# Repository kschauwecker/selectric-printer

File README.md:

# IBM Selectric Network Printer
This is an ongoing project to convert an IBM Selectric III electromechanical typewriter into a working network printer. It will consist of a set of solenoids that are linked through 3D-printed parts with the the typewrites mechanisms. A custom circuit board controls the solenoids, which features an RP2040 micro controller and a Raspberry Pi Compute Module.

Have a look at my other typewriter projects to get an idea what this will be like:
https://elektronaut.tech/en/tinker-corner/

More information will follow...

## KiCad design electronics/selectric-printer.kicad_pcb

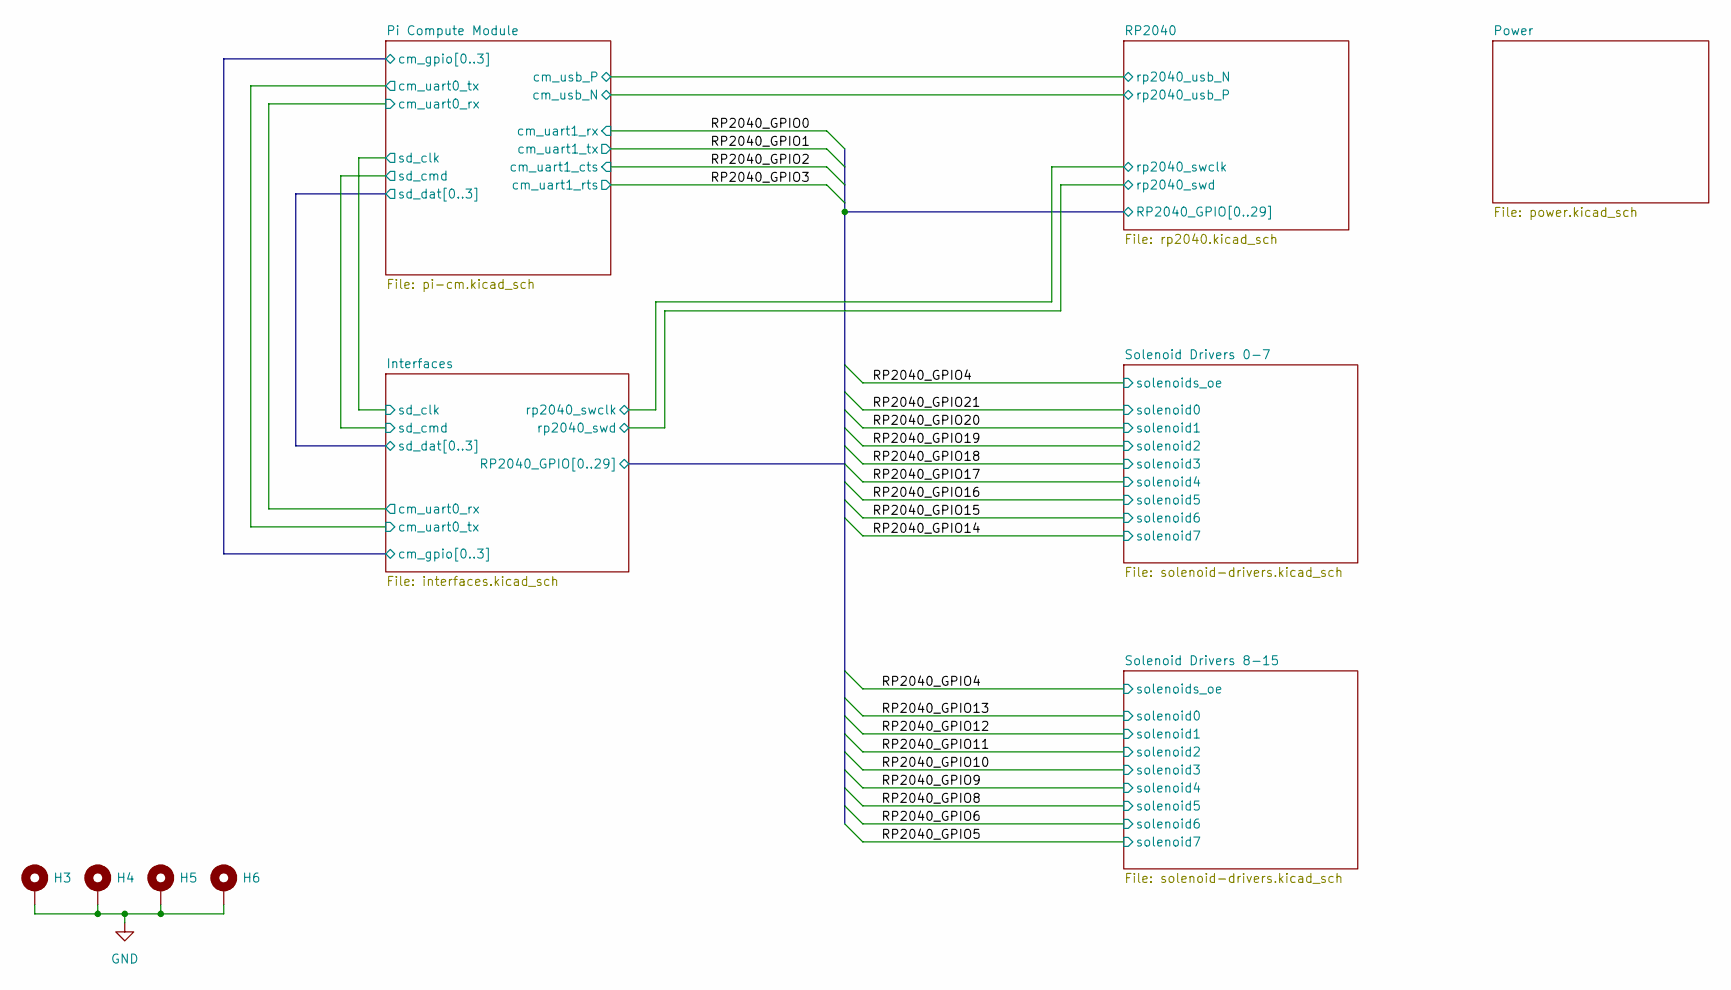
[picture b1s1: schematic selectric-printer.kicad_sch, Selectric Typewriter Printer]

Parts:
H3, H4, H5, H6: MountingHole_Pad; MountingHole_3.2mm_M3_Pad

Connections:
GND: H3.1, H4.1, H5.1, H6.1; also elsewhere on the board

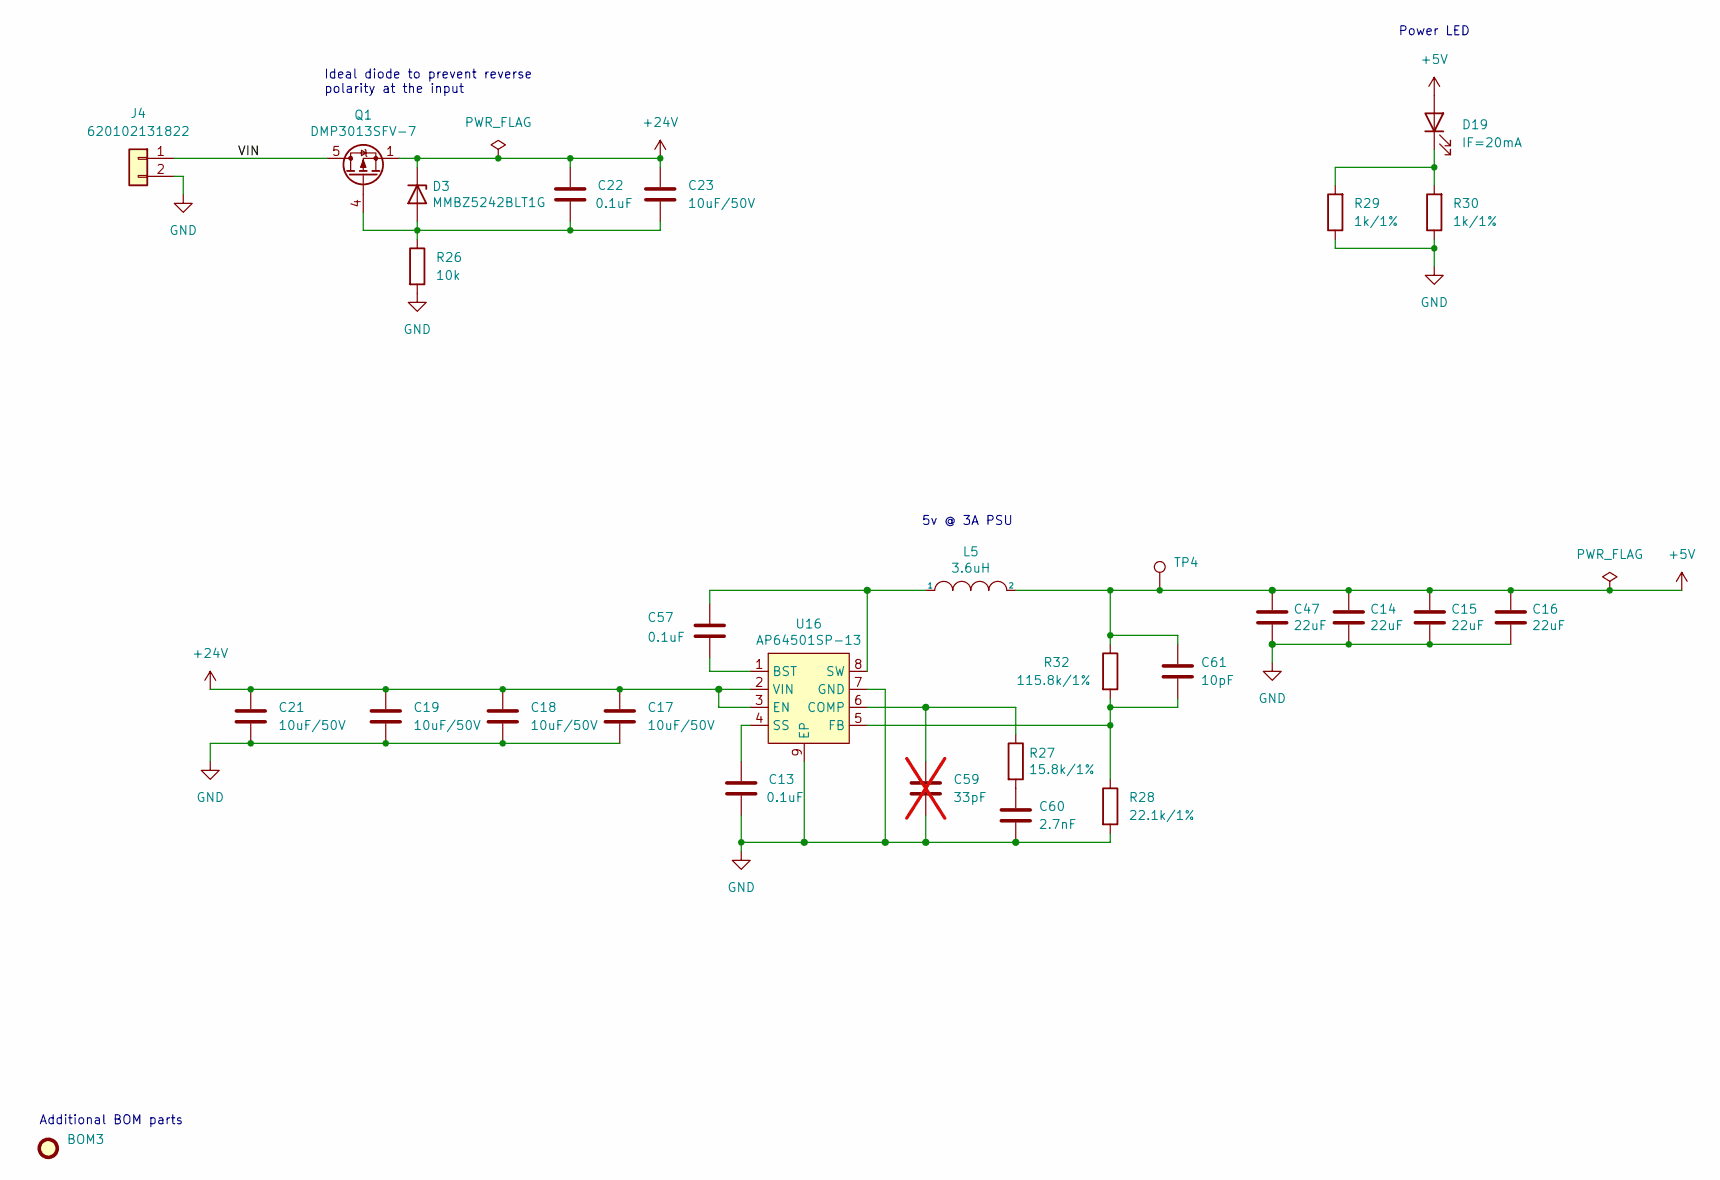
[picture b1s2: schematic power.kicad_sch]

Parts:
BOM3: MPN 620002113322
C13, C22, C57: 0.1uF; C_0402_1005Metric; MPN MBAST105SB7104KFNA01
C14, C15, C16, C47: 22uF; C_0805_2012Metric; MPN LMK212BC6226MG-T
C17, C18, C19, C21, C23: 10uF/50V; C_1206_3216Metric; MPN MLASG31LAB7106KTNB25
C59: 33pF; C_0402_1005Metric; not fitted
C60: 2.7nF; C_0402_1005Metric; MPN GRM1555C1H272GE01J
C61: 10pF; C_0402_1005Metric; MPN C0402C100K5HACAUTO
D3: MMBZ5242BLT1G; D_SOD-323; MPN MMSZ5242BS-7-F
D19: IF=20mA; LED_0603_1608Metric; MPN 150060GS83000
J4: 620102131822; WE-620102131822; MPN 620102131822
L5: 3.6uH; L_Taiyo-Yuden_NR-80xx; MPN NRS8040T3R6NJGJ
Q1: DMP3013SFV-7; Diodes_PowerDI3333-8; MPN DMP3013SFV-7
R26: 10k; R_0402_1005Metric; MPN CRCW040210K0FKEDC
R27: 15.8k/1%; R_0402_1005Metric; MPN ERA-2AEB1582X
R28: 22.1k/1%; R_0402_1005Metric; MPN 560112110099
R29, R30: 1k/1%; R_0402_1005Metric; MPN RC0402JR-7D1KL
R32: 115.8k/1%; R_0402_1005Metric; MPN RP73PF1E115RBTD
TP4: TestPoint; TestPoint_Pad_D2.0mm
U16: AP64501SP-13; SOIC-8-1EP_3.9x4.9mm_P1.27mm_EP2.29x3mm; MPN AP64501SP-13

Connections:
+5V: C14.1, C15.1, C16.1, C47.1, C61.1, D19.2 (A), L5.2, R32.1, TP4.1; also elsewhere on the board
+24V: C17.1, C18.1, C19.1, C21.1, C22.1, C23.1, D3.1 (K), Q1.1 (S), Q1.2 (S), Q1.3 (S), U16.2 (VIN), U16.3 (EN); also elsewhere on the board
/Power/VIN: J4.1, Q1.5 (D)
GND: C13.2, C14.2, C15.2, C16.2, C17.2, C18.2, C19.2, C21.2, C47.2, C59.2, C60.2, J4.2, R26.2, R28.2, R29.1, R30.1, U16.7 (GND), U16.9 (EP); also elsewhere on the board
unnamed: C60.1, R27.2
unnamed: C22.2, C23.2, D3.2 (A), Q1.4 (G), R26.1
unnamed: D19.1 (K), R29.2, R30.2
unnamed: C57.2, U16.1 (BST)
unnamed: C59.1, R27.1, U16.6 (COMP)
unnamed: C61.2, R28.1, R32.2, U16.5 (FB)
unnamed: C13.1, U16.4 (SS)
unnamed: C57.1, L5.1, U16.8 (SW)

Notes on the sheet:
5v @ 3A PSU
Power LED
Ideal diode to prevent reverse polarity at the input
Additional BOM parts

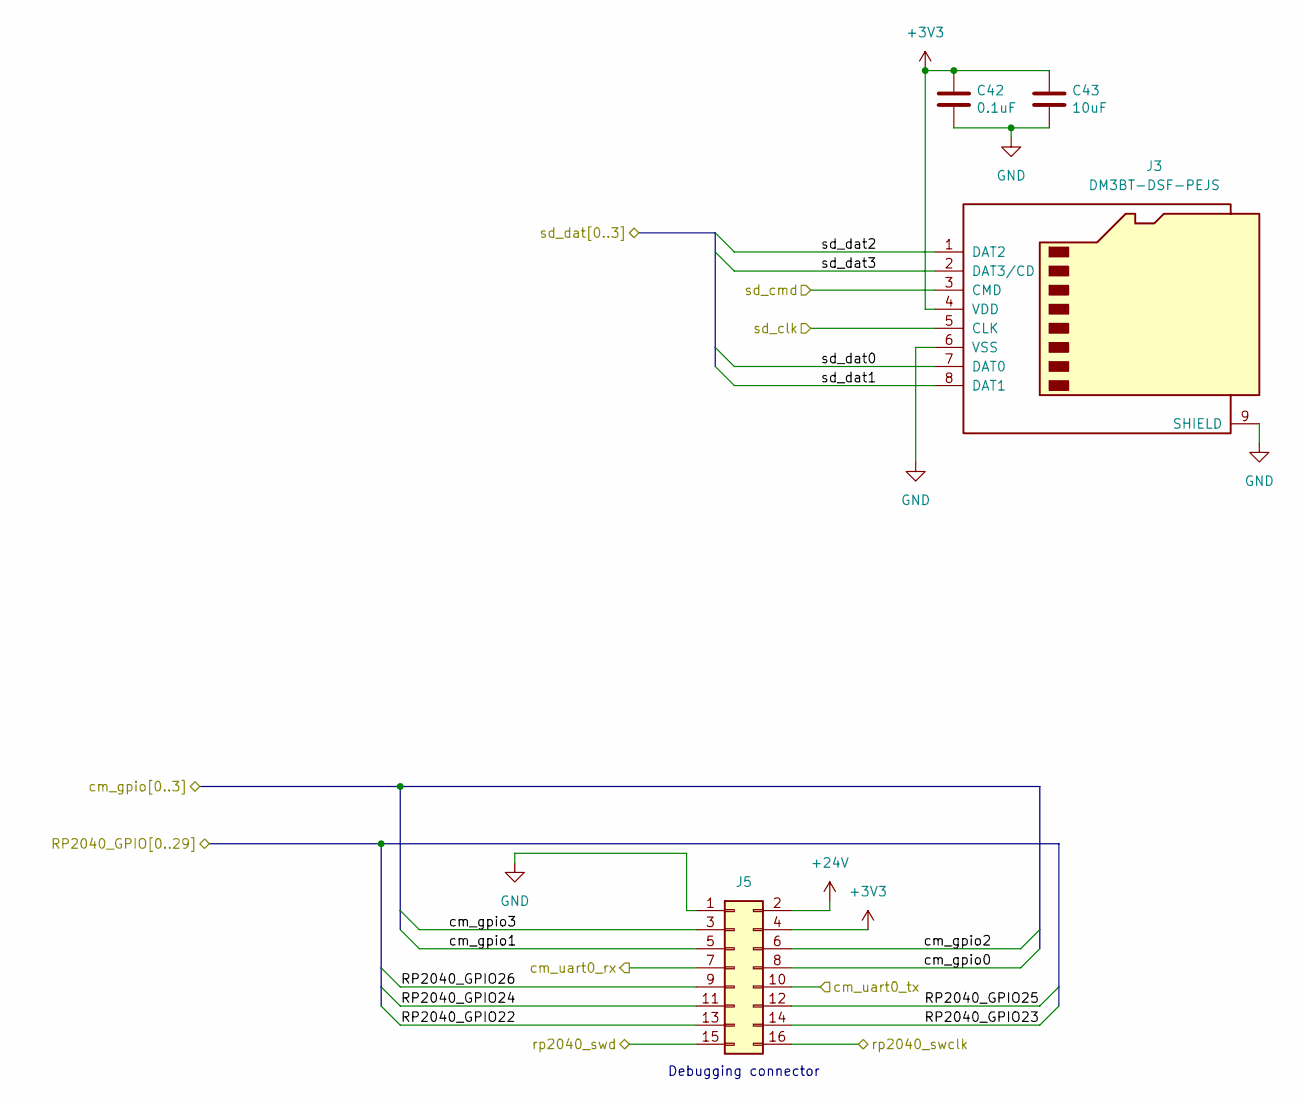
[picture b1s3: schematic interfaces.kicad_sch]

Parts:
C42: 0.1uF; C_0402_1005Metric; MPN MBAST105SB7104KFNA01
C43: 10uF; C_0603_1608Metric; MPN MSAST168BB5106MTNA01
J3: DM3BT-DSF-PEJS; microSD_HC_Hirose_DM3BT-DSF-PEJS; MPN DM3BT-DSF-PEJS
J5: Conn_02x08_Odd_Even; Samtec-TSM-108-01-F-DH; MPN TSM-108-01-F-DH

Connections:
+3V3: C42.1, C43.1, J3.4 (VDD), J5.4; also elsewhere on the board
+24V: J5.2; also elsewhere on the board
/Interfaces/RP2040_GPIO22: J5.13; also elsewhere on the board
/Interfaces/RP2040_GPIO23: J5.14; also elsewhere on the board
/Interfaces/RP2040_GPIO24: J5.11; also elsewhere on the board
/Interfaces/RP2040_GPIO25: J5.12; also elsewhere on the board
/Interfaces/RP2040_GPIO26: J5.9; also elsewhere on the board
/Interfaces/cm_gpio0: J5.8; also elsewhere on the board
/Interfaces/cm_gpio1: J5.5; also elsewhere on the board
/Interfaces/cm_gpio2: J5.6; also elsewhere on the board
/Interfaces/cm_gpio3: J5.3; also elsewhere on the board
/Interfaces/cm_uart0_rx: J5.7; also elsewhere on the board
/Interfaces/cm_uart0_tx: J5.10; also elsewhere on the board
/Interfaces/rp2040_swclk: J5.16; also elsewhere on the board
/Interfaces/rp2040_swd: J5.15; also elsewhere on the board
/Interfaces/sd_cmd: J3.3 (CMD); also elsewhere on the board
/Interfaces/sd_dat0: J3.7 (DAT0); also elsewhere on the board
/Interfaces/sd_dat1: J3.8 (DAT1); also elsewhere on the board
/Interfaces/sd_dat2: J3.1 (DAT2); also elsewhere on the board
/Interfaces/sd_dat3: J3.2 (DAT3/CD); also elsewhere on the board
/Pi Compute Module/sd_clk: J3.5 (CLK); also elsewhere on the board
GND: C42.2, C43.2, J3.6 (VSS), J3.9 (SHIELD), J5.1; also elsewhere on the board

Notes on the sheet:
Debugging connector

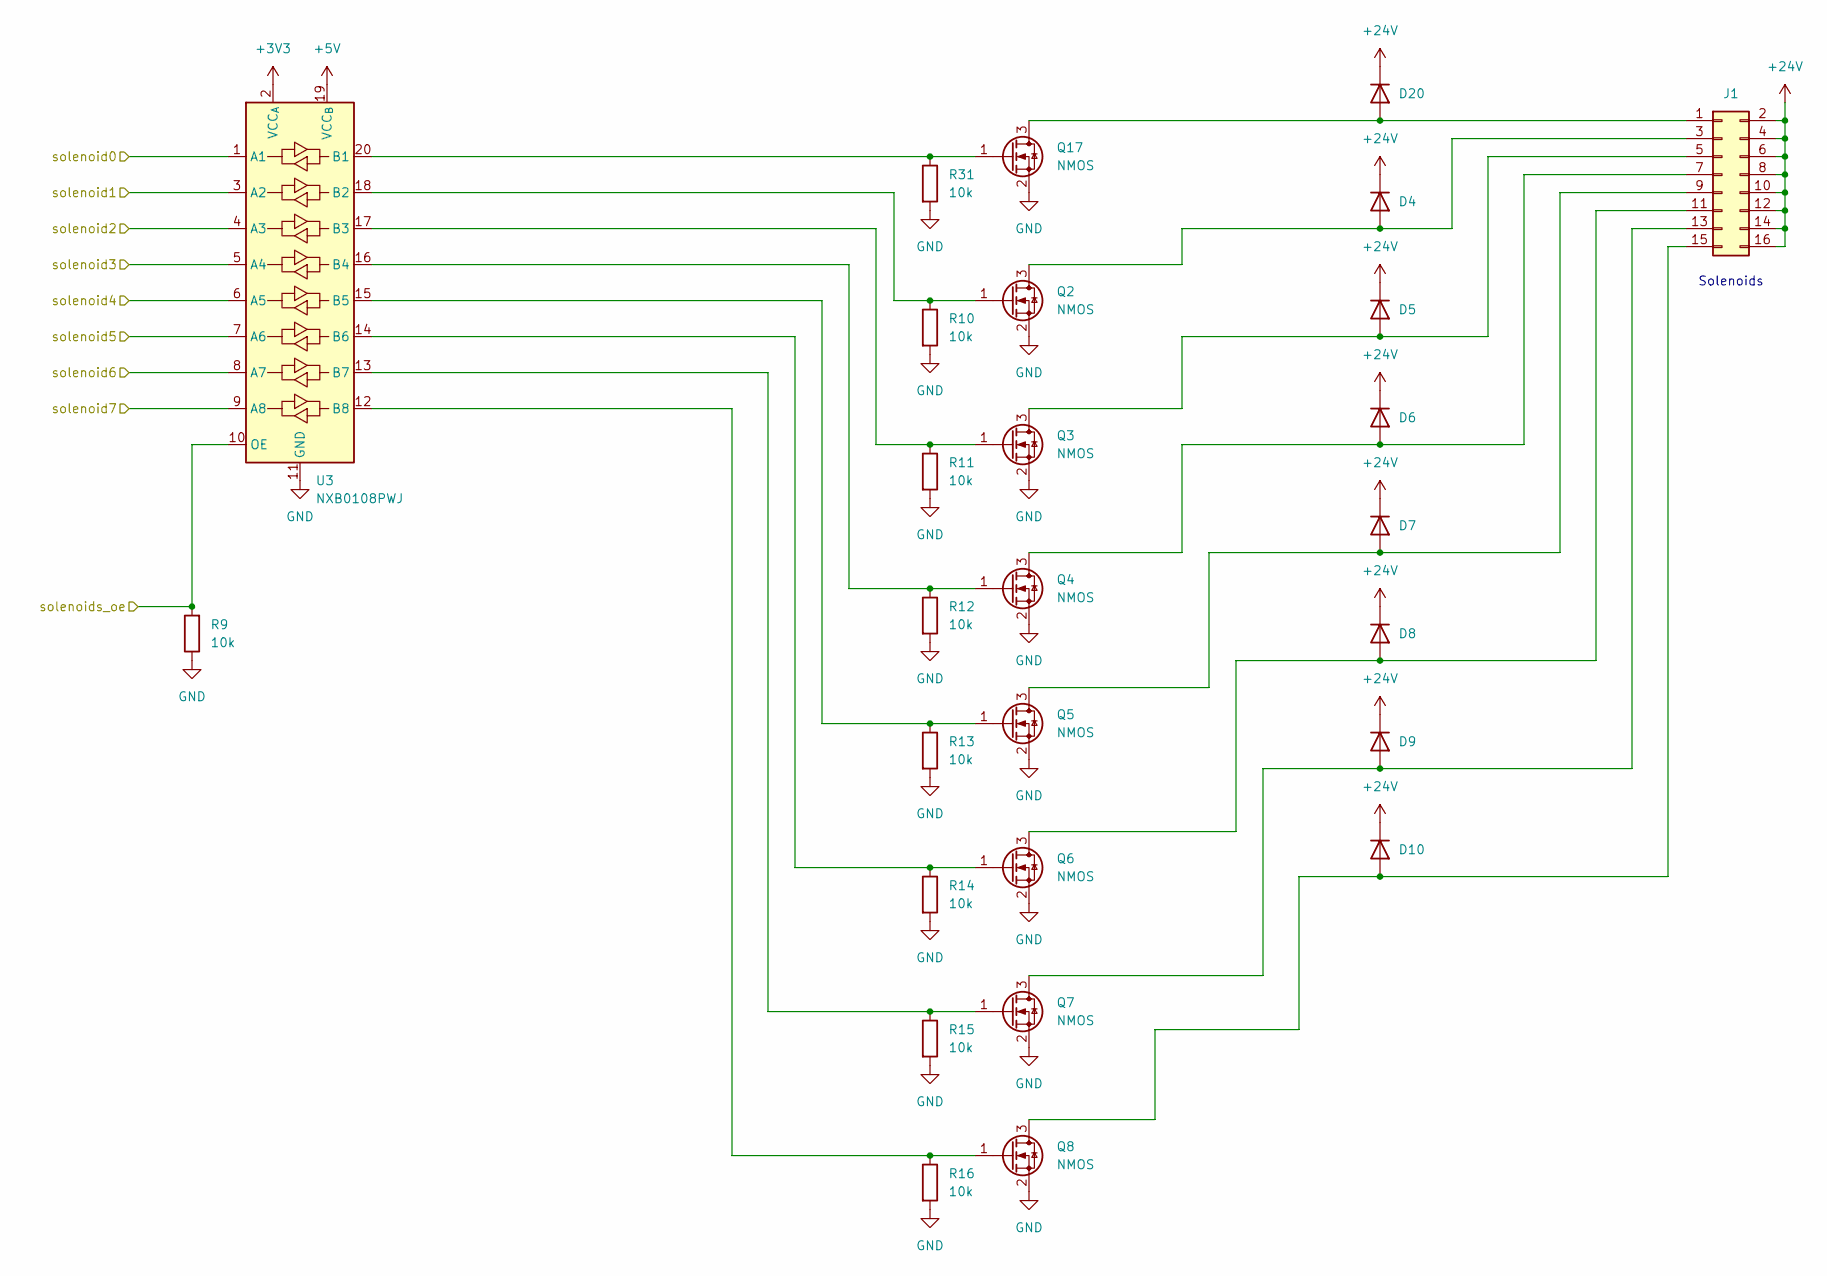
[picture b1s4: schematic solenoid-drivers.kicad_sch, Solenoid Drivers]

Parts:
D4, D5, D6, D7, D8, D9, D10, D20: D; D_PowerDI-123; MPN SBR3U60P1-7
J1: Conn_02x08_Odd_Even; Samtec-TSM-108-01-F-DH; MPN TSM-108-01-F-DH
Q2, Q3, Q4, Q5, Q6, Q7, Q8, Q17: NMOS; SOT-23-3; MPN DMN6140LQ-7
R9, R10, R11, R12, R13, R14, R15, R16, R31: 10k; R_0402_1005Metric; MPN CRCW040210K0FKEDC
U3: NXB0108PWJ; TSSOP-20_4.4x6.5mm_P0.65mm; MPN NXB0108PWJ

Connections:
+3V3: U3.2 (VCC_{A}); also elsewhere on the board
+5V: U3.19 (VCC_{B}); also elsewhere on the board
+24V: D4.1 (K), D5.1 (K), D6.1 (K), D7.1 (K), D8.1 (K), D9.1 (K), D10.1 (K), D20.1 (K), J1.2, J1.4, J1.6, J1.8, J1.10, J1.12, J1.14, J1.16; also elsewhere on the board
/Interfaces/RP2040_GPIO4: R9.2, U3.10 (OE); also elsewhere on the board
/Interfaces/RP2040_GPIO14: U3.9 (A8); also elsewhere on the board
/Interfaces/RP2040_GPIO15: U3.8 (A7); also elsewhere on the board
/Interfaces/RP2040_GPIO16: U3.7 (A6); also elsewhere on the board
/Interfaces/RP2040_GPIO17: U3.6 (A5); also elsewhere on the board
/Interfaces/RP2040_GPIO18: U3.5 (A4); also elsewhere on the board
/Interfaces/RP2040_GPIO19: U3.4 (A3); also elsewhere on the board
/Interfaces/RP2040_GPIO20: U3.3 (A2); also elsewhere on the board
/Interfaces/RP2040_GPIO21: U3.1 (A1); also elsewhere on the board
GND: Q2.2 (S), Q3.2 (S), Q4.2 (S), Q5.2 (S), Q6.2 (S), Q7.2 (S), Q8.2 (S), Q17.2 (S), R9.1, R10.2, R11.2, R12.2, R13.2, R14.2, R15.2, R16.2, R31.2, U3.11 (GND); also elsewhere on the board
unnamed: D4.2 (A), J1.3, Q2.3 (D)
unnamed: D5.2 (A), J1.5, Q3.3 (D)
unnamed: D6.2 (A), J1.7, Q4.3 (D)
unnamed: D7.2 (A), J1.9, Q5.3 (D)
unnamed: D8.2 (A), J1.11, Q6.3 (D)
unnamed: D9.2 (A), J1.13, Q7.3 (D)
unnamed: D10.2 (A), J1.15, Q8.3 (D)
unnamed: D20.2 (A), J1.1, Q17.3 (D)
unnamed: Q2.1 (G), R10.1, U3.18 (B2)
unnamed: Q3.1 (G), R11.1, U3.17 (B3)
unnamed: Q4.1 (G), R12.1, U3.16 (B4)
unnamed: Q5.1 (G), R13.1, U3.15 (B5)
unnamed: Q6.1 (G), R14.1, U3.14 (B6)
unnamed: Q7.1 (G), R15.1, U3.13 (B7)
unnamed: Q8.1 (G), R16.1, U3.12 (B8)
unnamed: Q17.1 (G), R31.1, U3.20 (B1)

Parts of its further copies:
D11, D12, D13, D14, D15, D16, D17, D18: D; D_PowerDI-123; MPN SBR3U60P1-7
J2: Conn_02x08_Odd_Even; Samtec-TSM-108-01-F-DH; MPN TSM-108-01-F-DH
Q9, Q10, Q11, Q12, Q13, Q14, Q15, Q16: NMOS; SOT-23-3; MPN DMN6140LQ-7
R17, R18, R19, R20, R21, R22, R23, R24, R25: 10k; R_0402_1005Metric; MPN CRCW040210K0FKEDC
U4: NXB0108PWJ; TSSOP-20_4.4x6.5mm_P0.65mm; MPN NXB0108PWJ

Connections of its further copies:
+3V3: U4.2 (VCC_{A}); also elsewhere on the board
+5V: U4.19 (VCC_{B}); also elsewhere on the board
+24V: D11.1 (K), D12.1 (K), D13.1 (K), D14.1 (K), D15.1 (K), D16.1 (K), D17.1 (K), D18.1 (K), J2.2, J2.4, J2.6, J2.8, J2.10, J2.12, J2.14, J2.16; also elsewhere on the board
/Interfaces/RP2040_GPIO4: R17.2, U4.10 (OE); also elsewhere on the board
/Interfaces/RP2040_GPIO5: U4.9 (A8); also elsewhere on the board
/Interfaces/RP2040_GPIO6: U4.8 (A7); also elsewhere on the board
/Interfaces/RP2040_GPIO8: U4.7 (A6); also elsewhere on the board
/Interfaces/RP2040_GPIO9: U4.6 (A5); also elsewhere on the board
/Interfaces/RP2040_GPIO10: U4.5 (A4); also elsewhere on the board
/Interfaces/RP2040_GPIO11: U4.4 (A3); also elsewhere on the board
/Interfaces/RP2040_GPIO12: U4.3 (A2); also elsewhere on the board
/Interfaces/RP2040_GPIO13: U4.1 (A1); also elsewhere on the board
GND: Q9.2 (S), Q10.2 (S), Q11.2 (S), Q12.2 (S), Q13.2 (S), Q14.2 (S), Q15.2 (S), Q16.2 (S), R17.1, R18.2, R19.2, R20.2, R21.2, R22.2, R23.2, R24.2, R25.2, U4.11 (GND); also elsewhere on the board
unnamed: D11.2 (A), J2.1, Q9.3 (D)
unnamed: D12.2 (A), J2.3, Q10.3 (D)
unnamed: D13.2 (A), J2.5, Q11.3 (D)
unnamed: D14.2 (A), J2.7, Q12.3 (D)
unnamed: D15.2 (A), J2.9, Q13.3 (D)
unnamed: D16.2 (A), J2.11, Q14.3 (D)
unnamed: D17.2 (A), J2.13, Q15.3 (D)
unnamed: D18.2 (A), J2.15, Q16.3 (D)
unnamed: Q9.1 (G), R18.1, U4.20 (B1)
unnamed: Q10.1 (G), R19.1, U4.18 (B2)
unnamed: Q11.1 (G), R20.1, U4.17 (B3)
unnamed: Q12.1 (G), R21.1, U4.16 (B4)
unnamed: Q13.1 (G), R22.1, U4.15 (B5)
unnamed: Q14.1 (G), R23.1, U4.14 (B6)
unnamed: Q15.1 (G), R24.1, U4.13 (B7)
unnamed: Q16.1 (G), R25.1, U4.12 (B8)

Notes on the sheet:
Solenoids

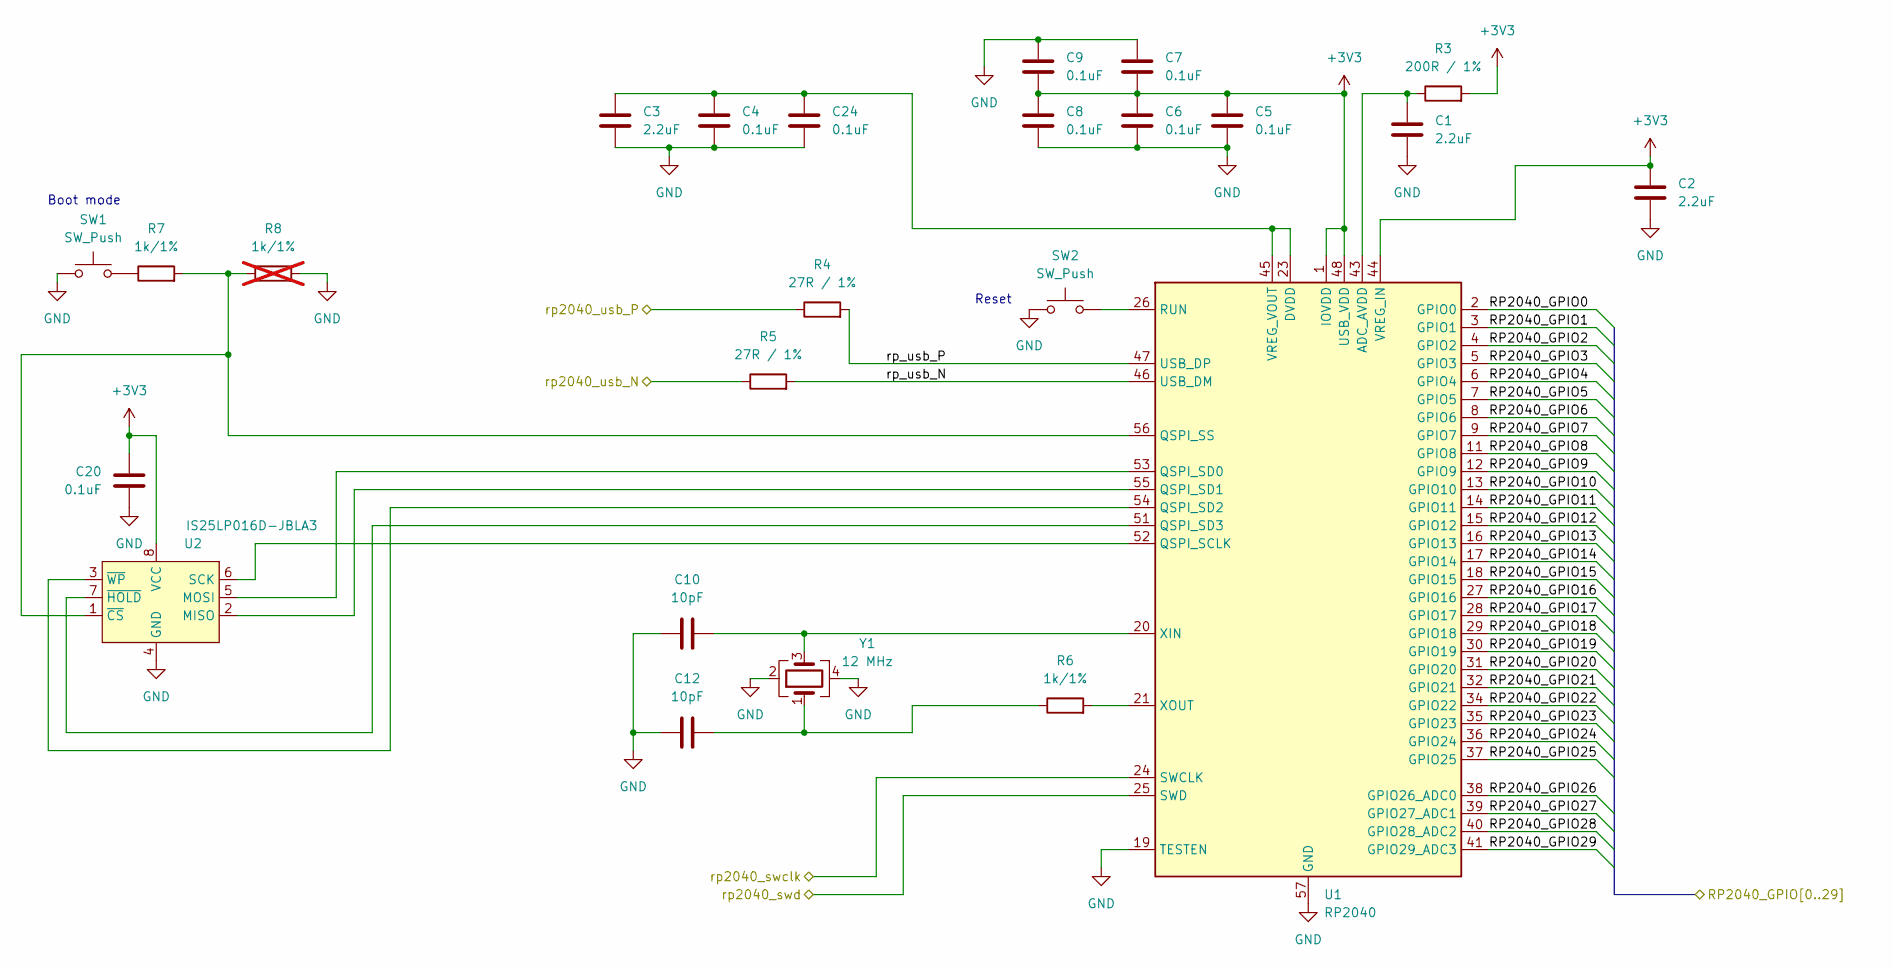
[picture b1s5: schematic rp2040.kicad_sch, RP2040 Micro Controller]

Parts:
C1, C2, C3: 2.2uF; C_0402_1005Metric; MPN GRM155C80J225KE95J
C4, C5, C6, C7, C8, C9, C20, C24: 0.1uF; C_0402_1005Metric; MPN MBAST105SB7104KFNA01
C10, C12: 10pF; C_0402_1005Metric; MPN C0402C100K5HACAUTO
R3: 200R / 1%; R_0402_1005Metric; MPN CRCW0402200RFKEDHP
R4, R5: 27R / 1%; R_0402_1005Metric; MPN AC0402FR-0727RL
R6, R7: 1k/1%; R_0402_1005Metric; MPN RC0402JR-7D1KL
R8: 1k/1%; R_0402_1005Metric; MPN RC0402JR-7D1KL; not fitted
SW1, SW2: SW_Push; SW_Push_1P1T_NO_CK_KSC7xxJ; MPN KSC721J LFS
U1: RP2040; QFN-56-1EP_7x7mm_P0.4mm_EP3.2x3.2mm; MPN SC0914(13)
U2: IS25LP016D-JBLA3; SOIC-8; MPN IS25LP016D-JBLA3
Y1: 12 MHz; Crystal_SMD_Abracon_ABM8G-4Pin_3.2x2.5mm; MPN ABM8-272-T3

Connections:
+3V3: C2.1, C5.1, C6.1, C7.2, C8.1, C9.2, C20.1, R3.2, U1.1 (IOVDD), U1.10 (IOVDD), U1.22 (IOVDD), U1.33 (IOVDD), U1.42 (IOVDD), U1.44 (VREG_IN), U1.48 (USB_VDD), U1.49 (IOVDD), U2.8 (VCC); also elsewhere on the board
/Interfaces/RP2040_GPIO0: U1.2 (GPIO0); also elsewhere on the board
/Interfaces/RP2040_GPIO1: U1.3 (GPIO1); also elsewhere on the board
/Interfaces/RP2040_GPIO2: U1.4 (GPIO2); also elsewhere on the board
/Interfaces/RP2040_GPIO3: U1.5 (GPIO3); also elsewhere on the board
/Interfaces/RP2040_GPIO4: U1.6 (GPIO4); also elsewhere on the board
/Interfaces/RP2040_GPIO5: U1.7 (GPIO5); also elsewhere on the board
/Interfaces/RP2040_GPIO6: U1.8 (GPIO6); also elsewhere on the board
/Interfaces/RP2040_GPIO7: U1.9 (GPIO7)
/Interfaces/RP2040_GPIO8: U1.11 (GPIO8); also elsewhere on the board
/Interfaces/RP2040_GPIO9: U1.12 (GPIO9); also elsewhere on the board
/Interfaces/RP2040_GPIO10: U1.13 (GPIO10); also elsewhere on the board
/Interfaces/RP2040_GPIO11: U1.14 (GPIO11); also elsewhere on the board
/Interfaces/RP2040_GPIO12: U1.15 (GPIO12); also elsewhere on the board
/Interfaces/RP2040_GPIO13: U1.16 (GPIO13); also elsewhere on the board
/Interfaces/RP2040_GPIO14: U1.17 (GPIO14); also elsewhere on the board
/Interfaces/RP2040_GPIO15: U1.18 (GPIO15); also elsewhere on the board
/Interfaces/RP2040_GPIO16: U1.27 (GPIO16); also elsewhere on the board
/Interfaces/RP2040_GPIO17: U1.28 (GPIO17); also elsewhere on the board
/Interfaces/RP2040_GPIO18: U1.29 (GPIO18); also elsewhere on the board
/Interfaces/RP2040_GPIO19: U1.30 (GPIO19); also elsewhere on the board
/Interfaces/RP2040_GPIO20: U1.31 (GPIO20); also elsewhere on the board
/Interfaces/RP2040_GPIO21: U1.32 (GPIO21); also elsewhere on the board
/Interfaces/RP2040_GPIO22: U1.34 (GPIO22); also elsewhere on the board
/Interfaces/RP2040_GPIO23: U1.35 (GPIO23); also elsewhere on the board
/Interfaces/RP2040_GPIO24: U1.36 (GPIO24); also elsewhere on the board
/Interfaces/RP2040_GPIO25: U1.37 (GPIO25); also elsewhere on the board
/Interfaces/RP2040_GPIO26: U1.38 (GPIO26_ADC0); also elsewhere on the board
/Interfaces/RP2040_GPIO27: U1.39 (GPIO27_ADC1)
/Interfaces/RP2040_GPIO28: U1.40 (GPIO28_ADC2)
/Interfaces/RP2040_GPIO29: U1.41 (GPIO29_ADC3)
/Interfaces/rp2040_swclk: U1.24 (SWCLK); also elsewhere on the board
/Interfaces/rp2040_swd: U1.25 (SWD); also elsewhere on the board
/Pi Compute Module/cm_usb_N: R4.1; also elsewhere on the board
/Pi Compute Module/cm_usb_P: R5.1; also elsewhere on the board
/RP2040/rp_usb_N: R5.2, U1.46 (USB_DM)
/RP2040/rp_usb_P: R4.2, U1.47 (USB_DP)
GND: C1.2, C2.2, C3.2, C4.2, C5.2, C6.2, C7.1, C8.2, C9.1, C10.1, C12.1, C20.2, C24.2, R8.2, SW1.1, SW2.1, U1.19 (TESTEN), U1.57 (GND), U2.4 (GND), Y1.2, Y1.4; also elsewhere on the board
unnamed: C12.2, R6.1, Y1.1
unnamed: R7.1, SW1.2
unnamed: C1.1, R3.1, U1.43 (ADC_AVDD)
unnamed: U1.52 (QSPI_SCLK), U2.6 (SCK)
unnamed: U1.53 (QSPI_SD0), U2.5 (MOSI)
unnamed: U1.55 (QSPI_SD1), U2.2 (MISO)
unnamed: U1.54 (QSPI_SD2), U2.3 (~WP)
unnamed: U1.51 (QSPI_SD3), U2.7 (~HOLD)
unnamed: R7.2, R8.1, U1.56 (QSPI_SS), U2.1 (~CS)
unnamed: SW2.2, U1.26 (RUN)
unnamed: C3.1, C4.1, C24.1, U1.23 (DVDD), U1.45 (VREG_VOUT), U1.50 (DVDD)
unnamed: C10.2, U1.20 (XIN), Y1.3
unnamed: R6.2, U1.21 (XOUT)

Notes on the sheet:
Reset
Boot mode

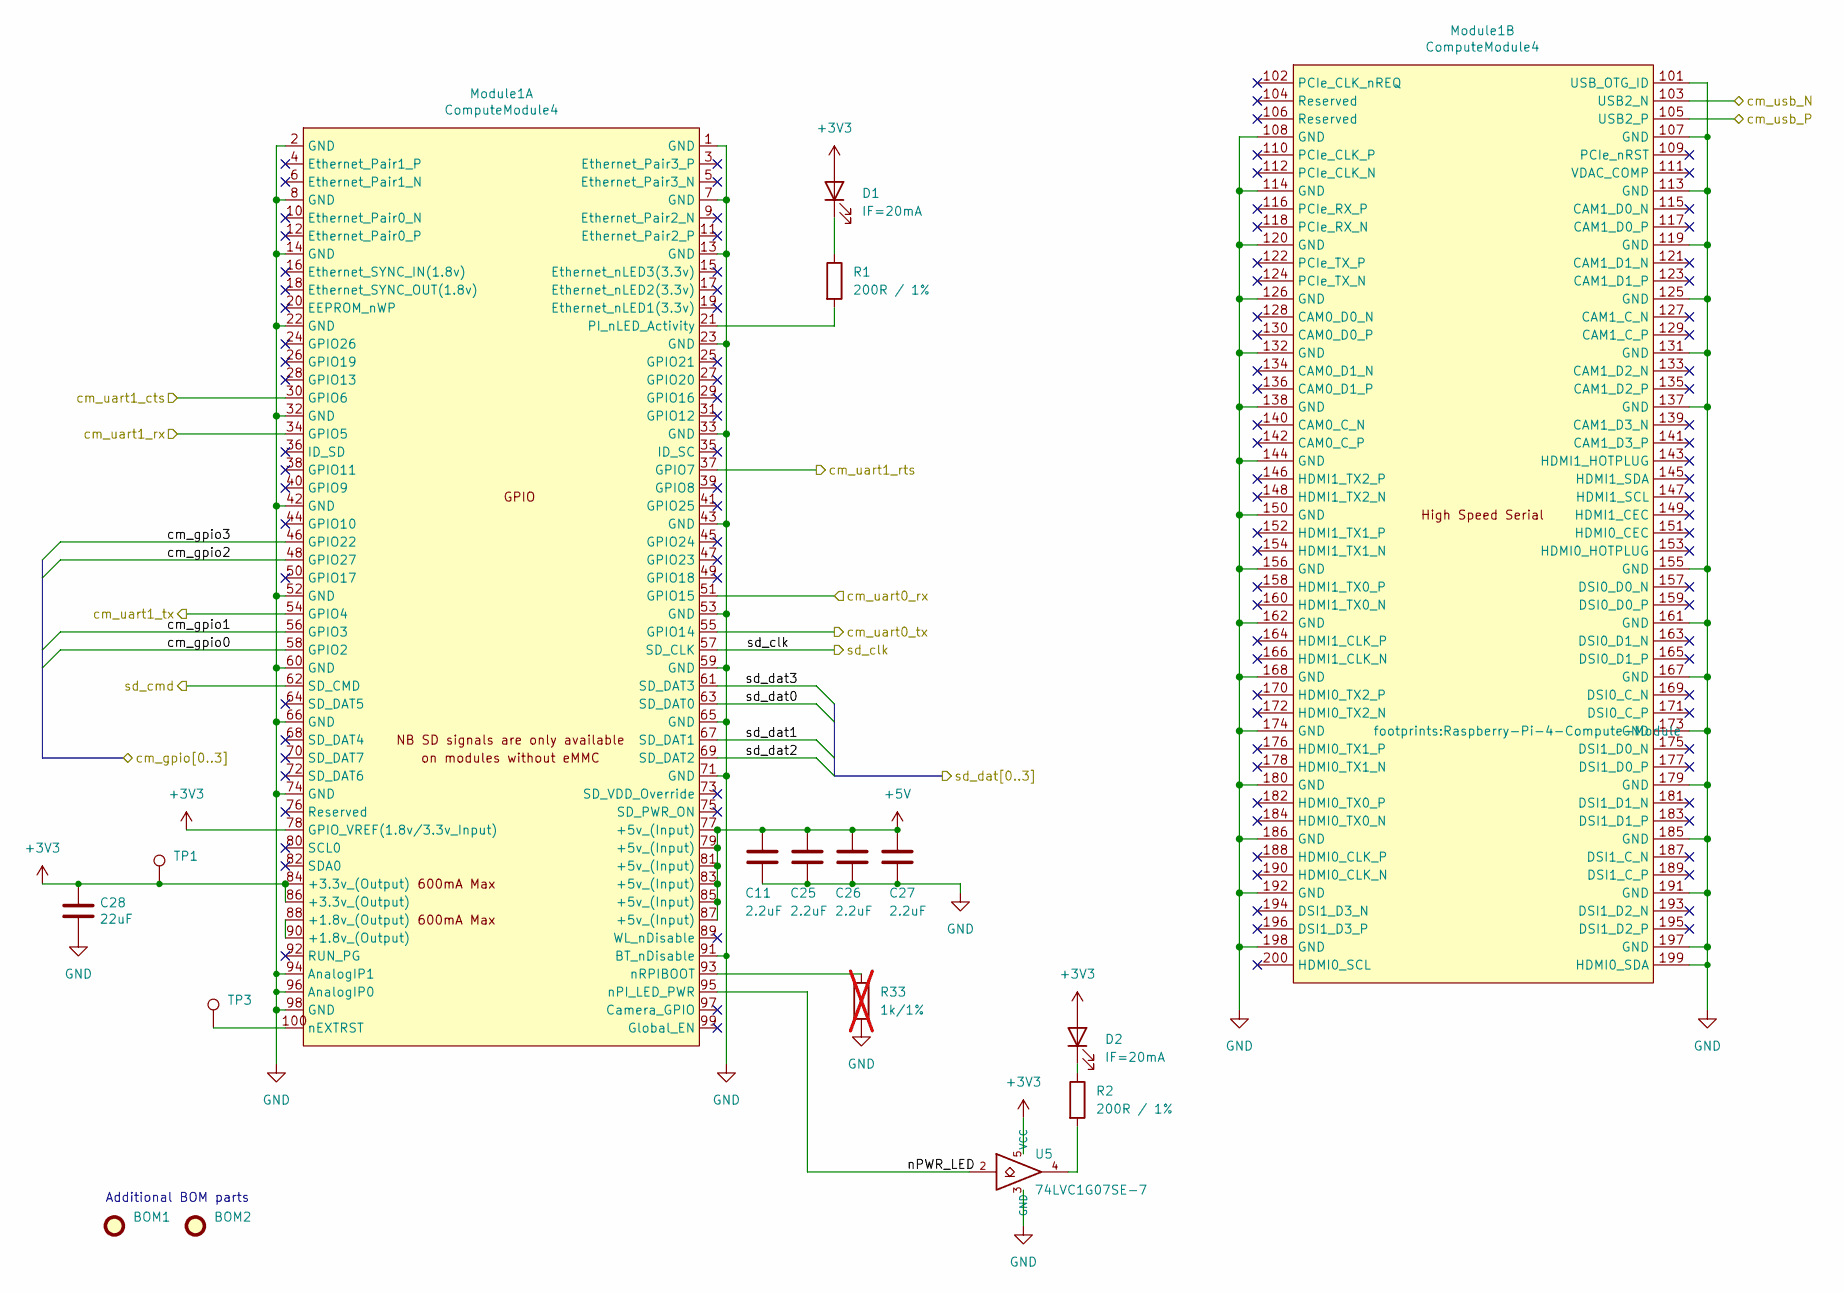
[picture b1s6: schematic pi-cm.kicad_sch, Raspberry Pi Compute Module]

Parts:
BOM1, BOM2: MPN DF40C-100DS-0.4V(51)
C11, C25, C26, C27: 2.2uF; C_0402_1005Metric; MPN GRM155C80J225KE95J
C28: 22uF; C_0805_2012Metric; MPN LMK212BC6226MG-T
D1, D2: IF=20mA; LED_0603_1608Metric; MPN 150060GS83000
Module1: ComputeModule4; Raspberry-Pi-4-Compute-Module
R1, R2: 200R / 1%; R_0402_1005Metric; MPN CRCW0402200RFKEDHP
R33: 1k/1%; R_0402_1005Metric; MPN RC0402JR-7D1KL; not fitted
TP1, TP3: TestPoint; TestPoint_Pad_D2.0mm
U5: 74LVC1G07SE-7; SOT-353_SC-70-5; MPN 74LVC1G07SE-7

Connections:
+3V3: C28.1, D1.2 (A), D2.2 (A), Module1.78 (GPIO_VREF(1.8v/3.3v_Input)), Module1.84 (+3.3v_(Output)), Module1.86 (+3.3v_(Output)), TP1.1, U5.5 (VCC); also elsewhere on the board
+5V: C11.1, C25.1, C26.1, C27.1, Module1.77 (+5v_(Input)), Module1.79 (+5v_(Input)), Module1.81 (+5v_(Input)), Module1.83 (+5v_(Input)), Module1.85 (+5v_(Input)), Module1.87 (+5v_(Input)); also elsewhere on the board
/Interfaces/RP2040_GPIO0: Module1.34 (GPIO5); also elsewhere on the board
/Interfaces/RP2040_GPIO1: Module1.54 (GPIO4); also elsewhere on the board
/Interfaces/RP2040_GPIO2: Module1.30 (GPIO6); also elsewhere on the board
/Interfaces/RP2040_GPIO3: Module1.37 (GPIO7); also elsewhere on the board
/Interfaces/cm_gpio0: Module1.58 (GPIO2); also elsewhere on the board
/Interfaces/cm_gpio1: Module1.56 (GPIO3); also elsewhere on the board
/Interfaces/cm_gpio2: Module1.48 (GPIO27); also elsewhere on the board
/Interfaces/cm_gpio3: Module1.46 (GPIO22); also elsewhere on the board
/Interfaces/cm_uart0_rx: Module1.51 (GPIO15); also elsewhere on the board
/Interfaces/cm_uart0_tx: Module1.55 (GPIO14); also elsewhere on the board
/Interfaces/sd_cmd: Module1.62 (SD_CMD); also elsewhere on the board
/Interfaces/sd_dat0: Module1.63 (SD_DAT0); also elsewhere on the board
/Interfaces/sd_dat1: Module1.67 (SD_DAT1); also elsewhere on the board
/Interfaces/sd_dat2: Module1.69 (SD_DAT2); also elsewhere on the board
/Interfaces/sd_dat3: Module1.61 (SD_DAT3); also elsewhere on the board
/Pi Compute Module/cm_usb_N: Module1.103 (USB2_N); also elsewhere on the board
/Pi Compute Module/cm_usb_P: Module1.105 (USB2_P); also elsewhere on the board
/Pi Compute Module/nPWR_LED: Module1.95 (nPI_LED_PWR), U5.2
/Pi Compute Module/sd_clk: Module1.57 (SD_CLK); also elsewhere on the board
GND: C11.2, C25.2, C26.2, C27.2, C28.2, Module1.1 (GND), Module1.2 (GND), Module1.7 (GND), Module1.8 (GND), Module1.13 (GND), Module1.14 (GND), Module1.22 (GND), Module1.23 (GND), Module1.32 (GND), Module1.33 (GND), Module1.42 (GND), Module1.43 (GND), Module1.52 (GND), Module1.53 (GND), Module1.59 (GND), Module1.60 (GND), Module1.65 (GND), Module1.66 (GND), Module1.71 (GND), Module1.74 (GND), Module1.91 (BT_nDisable), Module1.94 (AnalogIP1), Module1.96 (AnalogIP0), Module1.98 (GND), Module1.101 (USB_OTG_ID), Module1.107 (GND), Module1.108 (GND), Module1.113 (GND), Module1.114 (GND), Module1.119 (GND), Module1.120 (GND), Module1.125 (GND), Module1.126 (GND), Module1.131 (GND), Module1.132 (GND), Module1.137 (GND), Module1.138 (GND), Module1.144 (GND), Module1.150 (GND), Module1.155 (GND), Module1.156 (GND), Module1.161 (GND), Module1.162 (GND), Module1.167 (GND), Module1.168 (GND), Module1.173 (GND), Module1.174 (GND), Module1.179 (GND), Module1.180 (GND), Module1.185 (GND), Module1.186 (GND), Module1.191 (GND), Module1.192 (GND), Module1.197 (GND), Module1.198 (GND), Module1.199 (HDMI0_SDA), R33.1, U5.3 (GND); also elsewhere on the board
unnamed: D1.1 (K), R1.1
unnamed: D2.1 (K), R2.1
unnamed: Module1.88 (+1.8v_(Output)), Module1.90 (+1.8v_(Output))
unnamed: Module1.21 (PI_nLED_Activity), R1.2
unnamed: Module1.100 (nEXTRST), TP3.1
unnamed: Module1.93 (nRPIBOOT), R33.2
unnamed: R2.2, U5.4

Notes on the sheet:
Additional BOM parts
